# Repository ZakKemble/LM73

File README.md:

# LM73 Temperature Sensor Library

[TI LM73](https://www.ti.com/product/LM73) Temperature sensor IC library for Arduino.

## Installing

Search for "LM73" in the Arduino library manager and check out some of the examples!

## Docs

|Method|Parameters|Returns|Description|
|---|---|---|---|
|LM73(<br>TwoWire& wire<br>)|**wire**:<br>I2C interface to use.<br>Valid values: `Wire`, `Wire1`, `Wire2` ... etc.|Instance of LM73|Constructor.|
|begin(<br>uint8_t address<br>)|**address**:<br>Sensor I2C Address<br>Valid values: see table below|void|Initializes instance.|
|ctrl(<br>uint8_t resolution,<br>bool busTimeout<br>)|**resolution**:<br>Temperature conversion resolution.<br>Lower resolution gives faster conversion times.<br>Valid values: `11`, `12`, `13` or `14`<br>**busTimeout**:<br>This is an SMBus feature.<br>It's usually best to disable it (`false`) to reduce power consumption.|void|Configure various parameters.|
|mode(<br>uint8_t mode<br>)|**mode**:<br>`0` = Continuous (default)<br>`1` = Low-power one-shot|void|Set conversion mode.|
|read()|-|**float**: The temperature|Reads the latest temperature conversion.|
|convert()|-|void|Start a new one-shot conversion.<br>Has no effect in continuous mode.|
|available()|-|**bool**:<br>`true`: One-shot conversion complete.<br>`false`: Busy|-|
|alertStatus()|-|**uint8_t**:<br>Bitwise state and flags<br>Bit 7-4: N/A<br>Bit 3: Alert status<br>Bit 2: High flag<br>Bit 1: Low flag<br>Bit 0: N/A|Reads alarm status and high/low temperature flags.<br>See datasheet for more info.|
|alertReset()|-|void|Clear alarm output.|
|alertConfig(<br>bool enable,<br>uint8_t polarity,<br>float upperLimit,<br>float lowerLimit<br>)|**enable**:<br>Enable alarm output.<br>**polarity**:<br>`0` = Active low (default).<br>`1` = Active high.<br>**upperLimit**:<br>Alarm trigger level.<br>**lowerLimit**:<br>Alarm clear level.|void|-|

## Device I2C Addresses

The I2C address of the sensor IC will depend on whether it's an `-0` or `-1` type and the state of its address pin.

|Address pin|LM73-0|LM73-1|
|---|---|---|
|Float|0x48|0x4C|
|Ground|0x49|0x4D|
|VDD|0x4A|0x4E|

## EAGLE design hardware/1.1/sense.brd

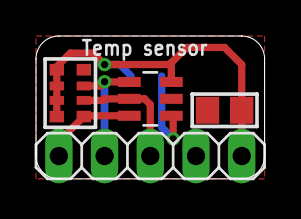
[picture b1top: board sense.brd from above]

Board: 2 copper layers, 12.7 x 7.9 mm, 5 parts (1 on the bottom side), 6 nets.

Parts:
C1: 100n; 0805
JP1: 1X05
RN1: 10K; RESPACK_4X0603
SJ1: SOLDERJUMPER_2WAY_OPEN_0603
U1: LM73CIMK-0; SOT95P285X100-6N

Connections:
ALERT: JP1.3, RN1.2, U1.5
GND: C1.2, JP1.4, SJ1.1, U1.2
unnamed: SJ1.2, U1.1
SCL: JP1.2, RN1.3, U1.4
SDA: JP1.1, RN1.1, U1.6
VCC: C1.1, JP1.5, RN1.5, RN1.6, RN1.7, RN1.8, SJ1.3, U1.3

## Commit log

2014-08-23 :lollipop: Added .gitattributes
2015-01-26 Typos
2015-12-20 Add category to library.properties
    Fixes the
    WARNING: Category '' in library LM73 is not valid. Setting to 'Uncategorized'
    warning in Arduino IDE 1.6.6 and 1.6.7.
2023-06-28 Reorganize files for inclusion into the Arduino Library Manager
2023-06-28 Major refactoring and simplification
2023-06-28 Minor fixes
2023-06-28 Update examples
2023-06-28 Rename `timeoutDisable` to `busTimeout`
2023-06-29 Change license from GPLv3 to MIT
2023-06-29 Bump to v2.0.0
2023-06-29 const correctness
2023-06-29 Rename `temperature()` to `read()`
2023-06-29 Bump to v2.1.0

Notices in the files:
parts and their libraries:
microbuilder: This work is placed in the public domain, and may be freely used for commercial and non-commercial work with the following conditions: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
